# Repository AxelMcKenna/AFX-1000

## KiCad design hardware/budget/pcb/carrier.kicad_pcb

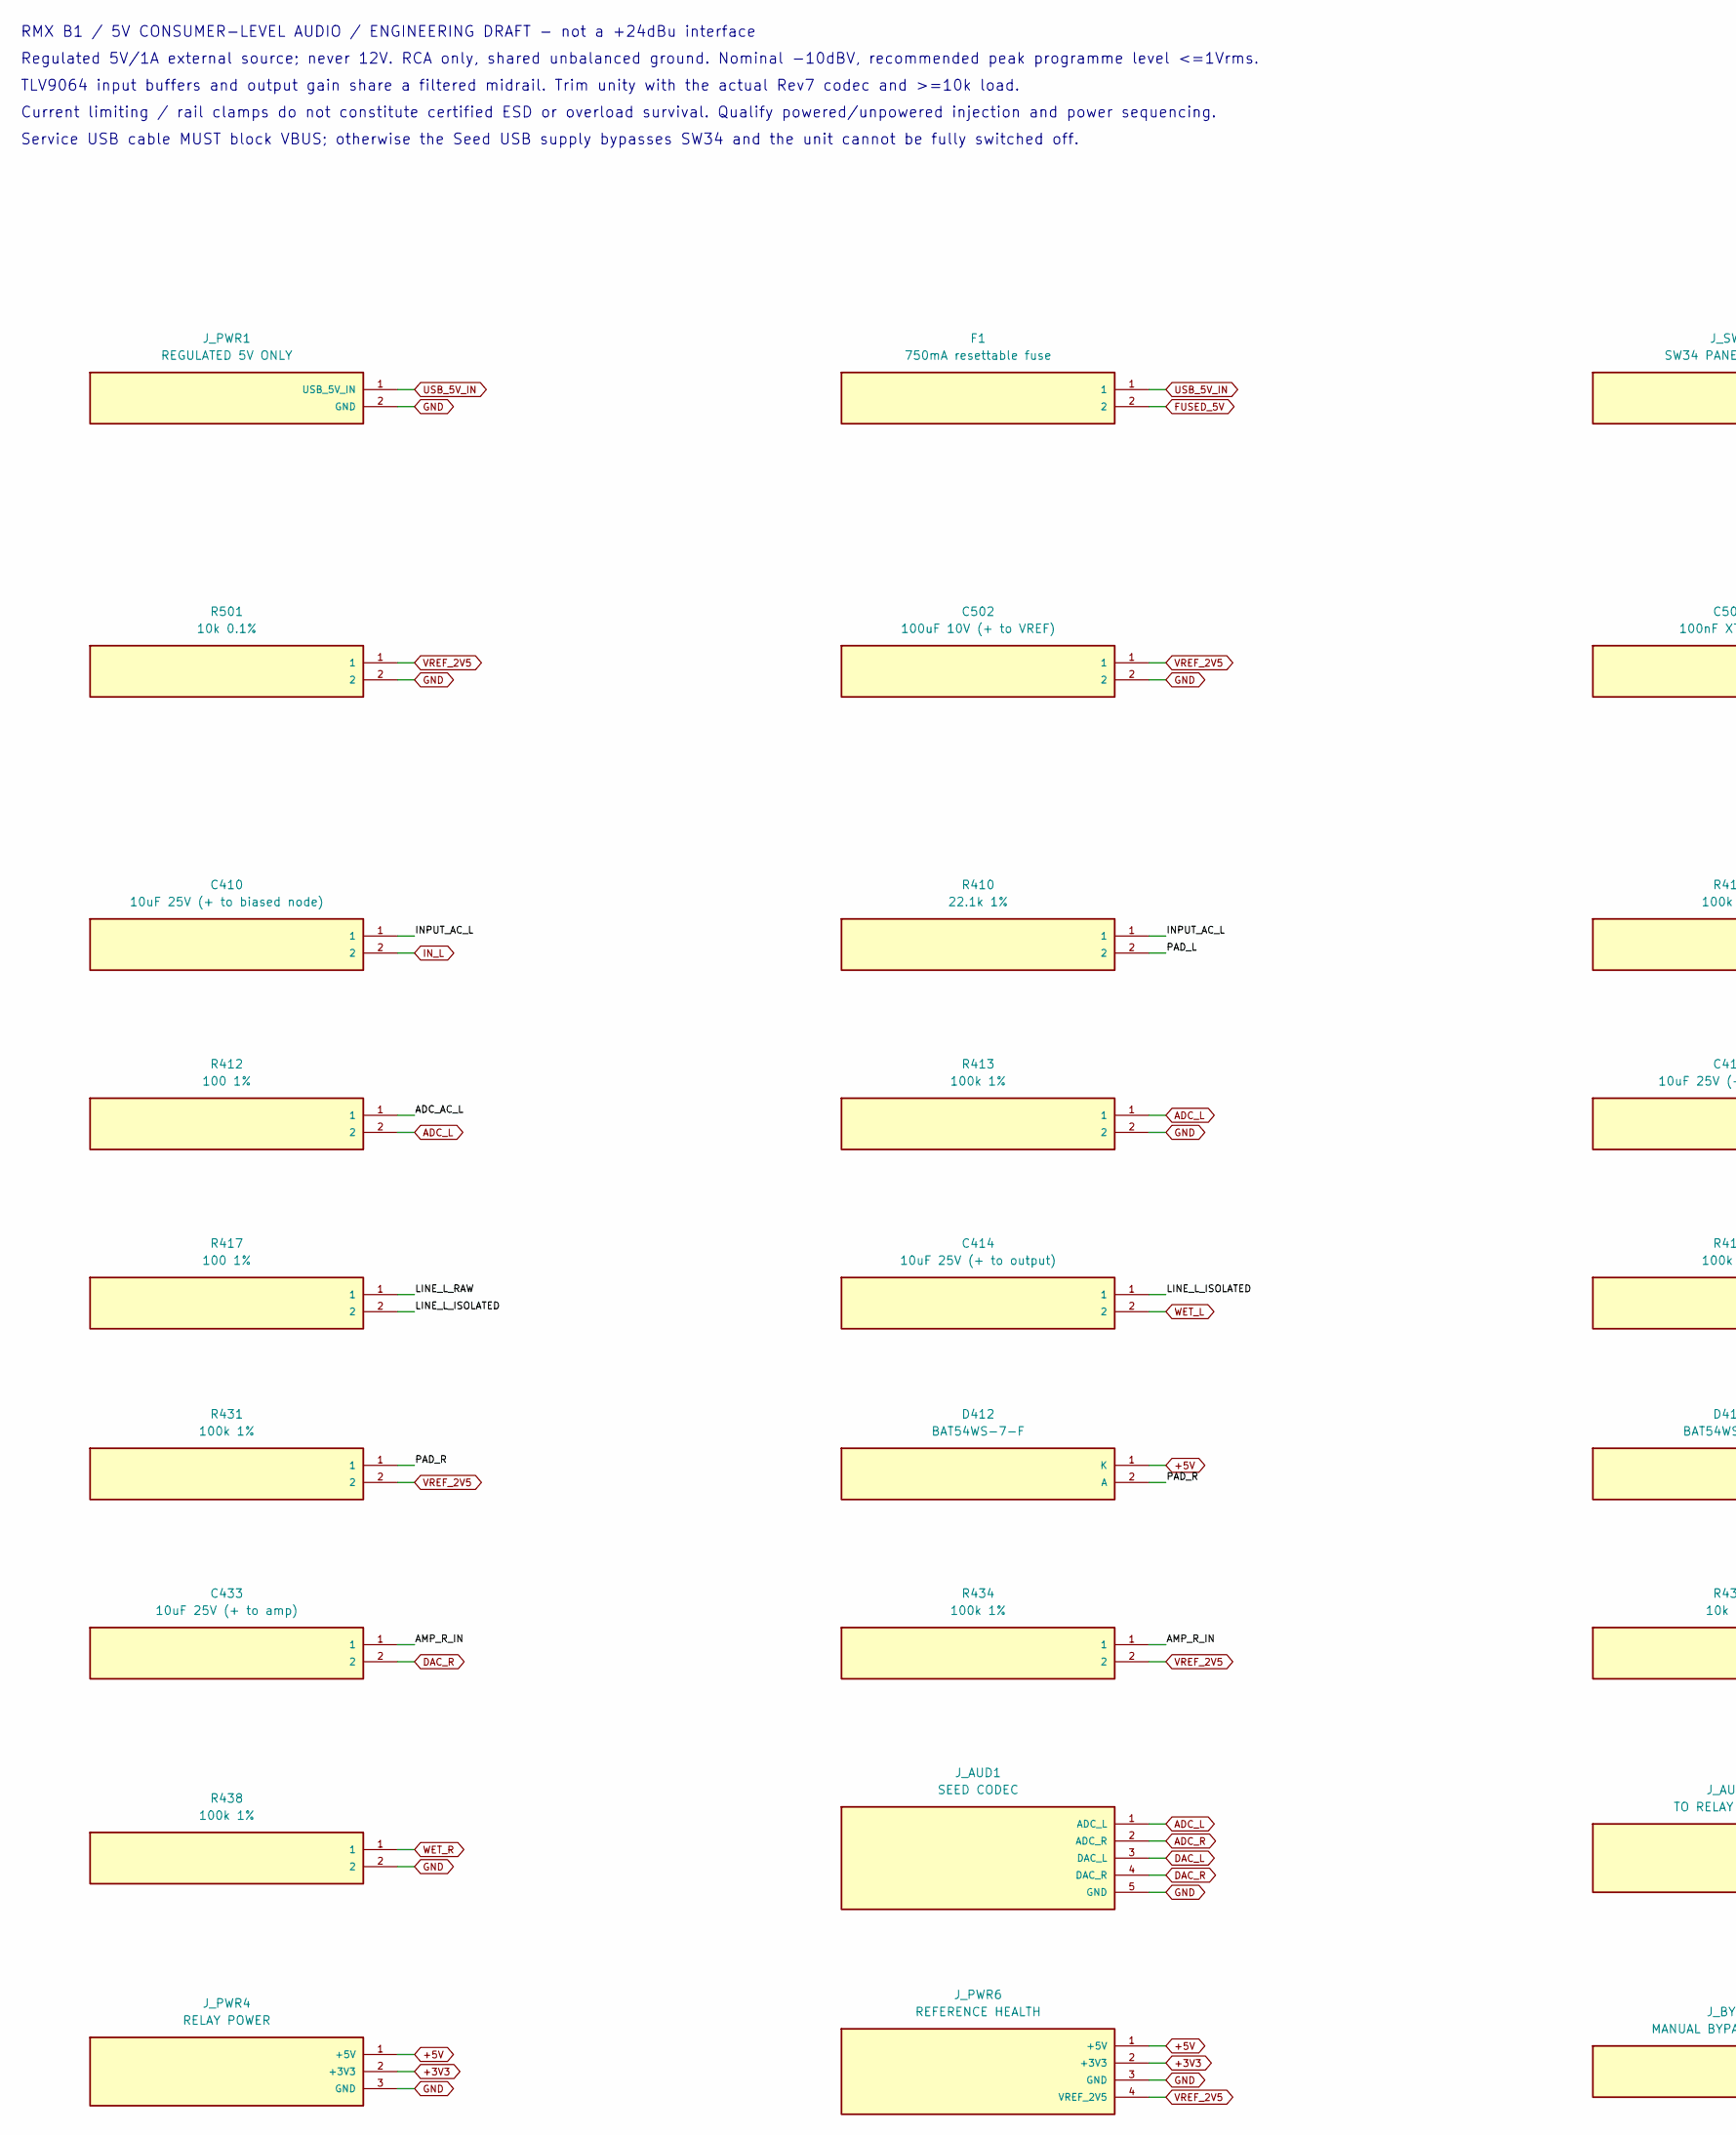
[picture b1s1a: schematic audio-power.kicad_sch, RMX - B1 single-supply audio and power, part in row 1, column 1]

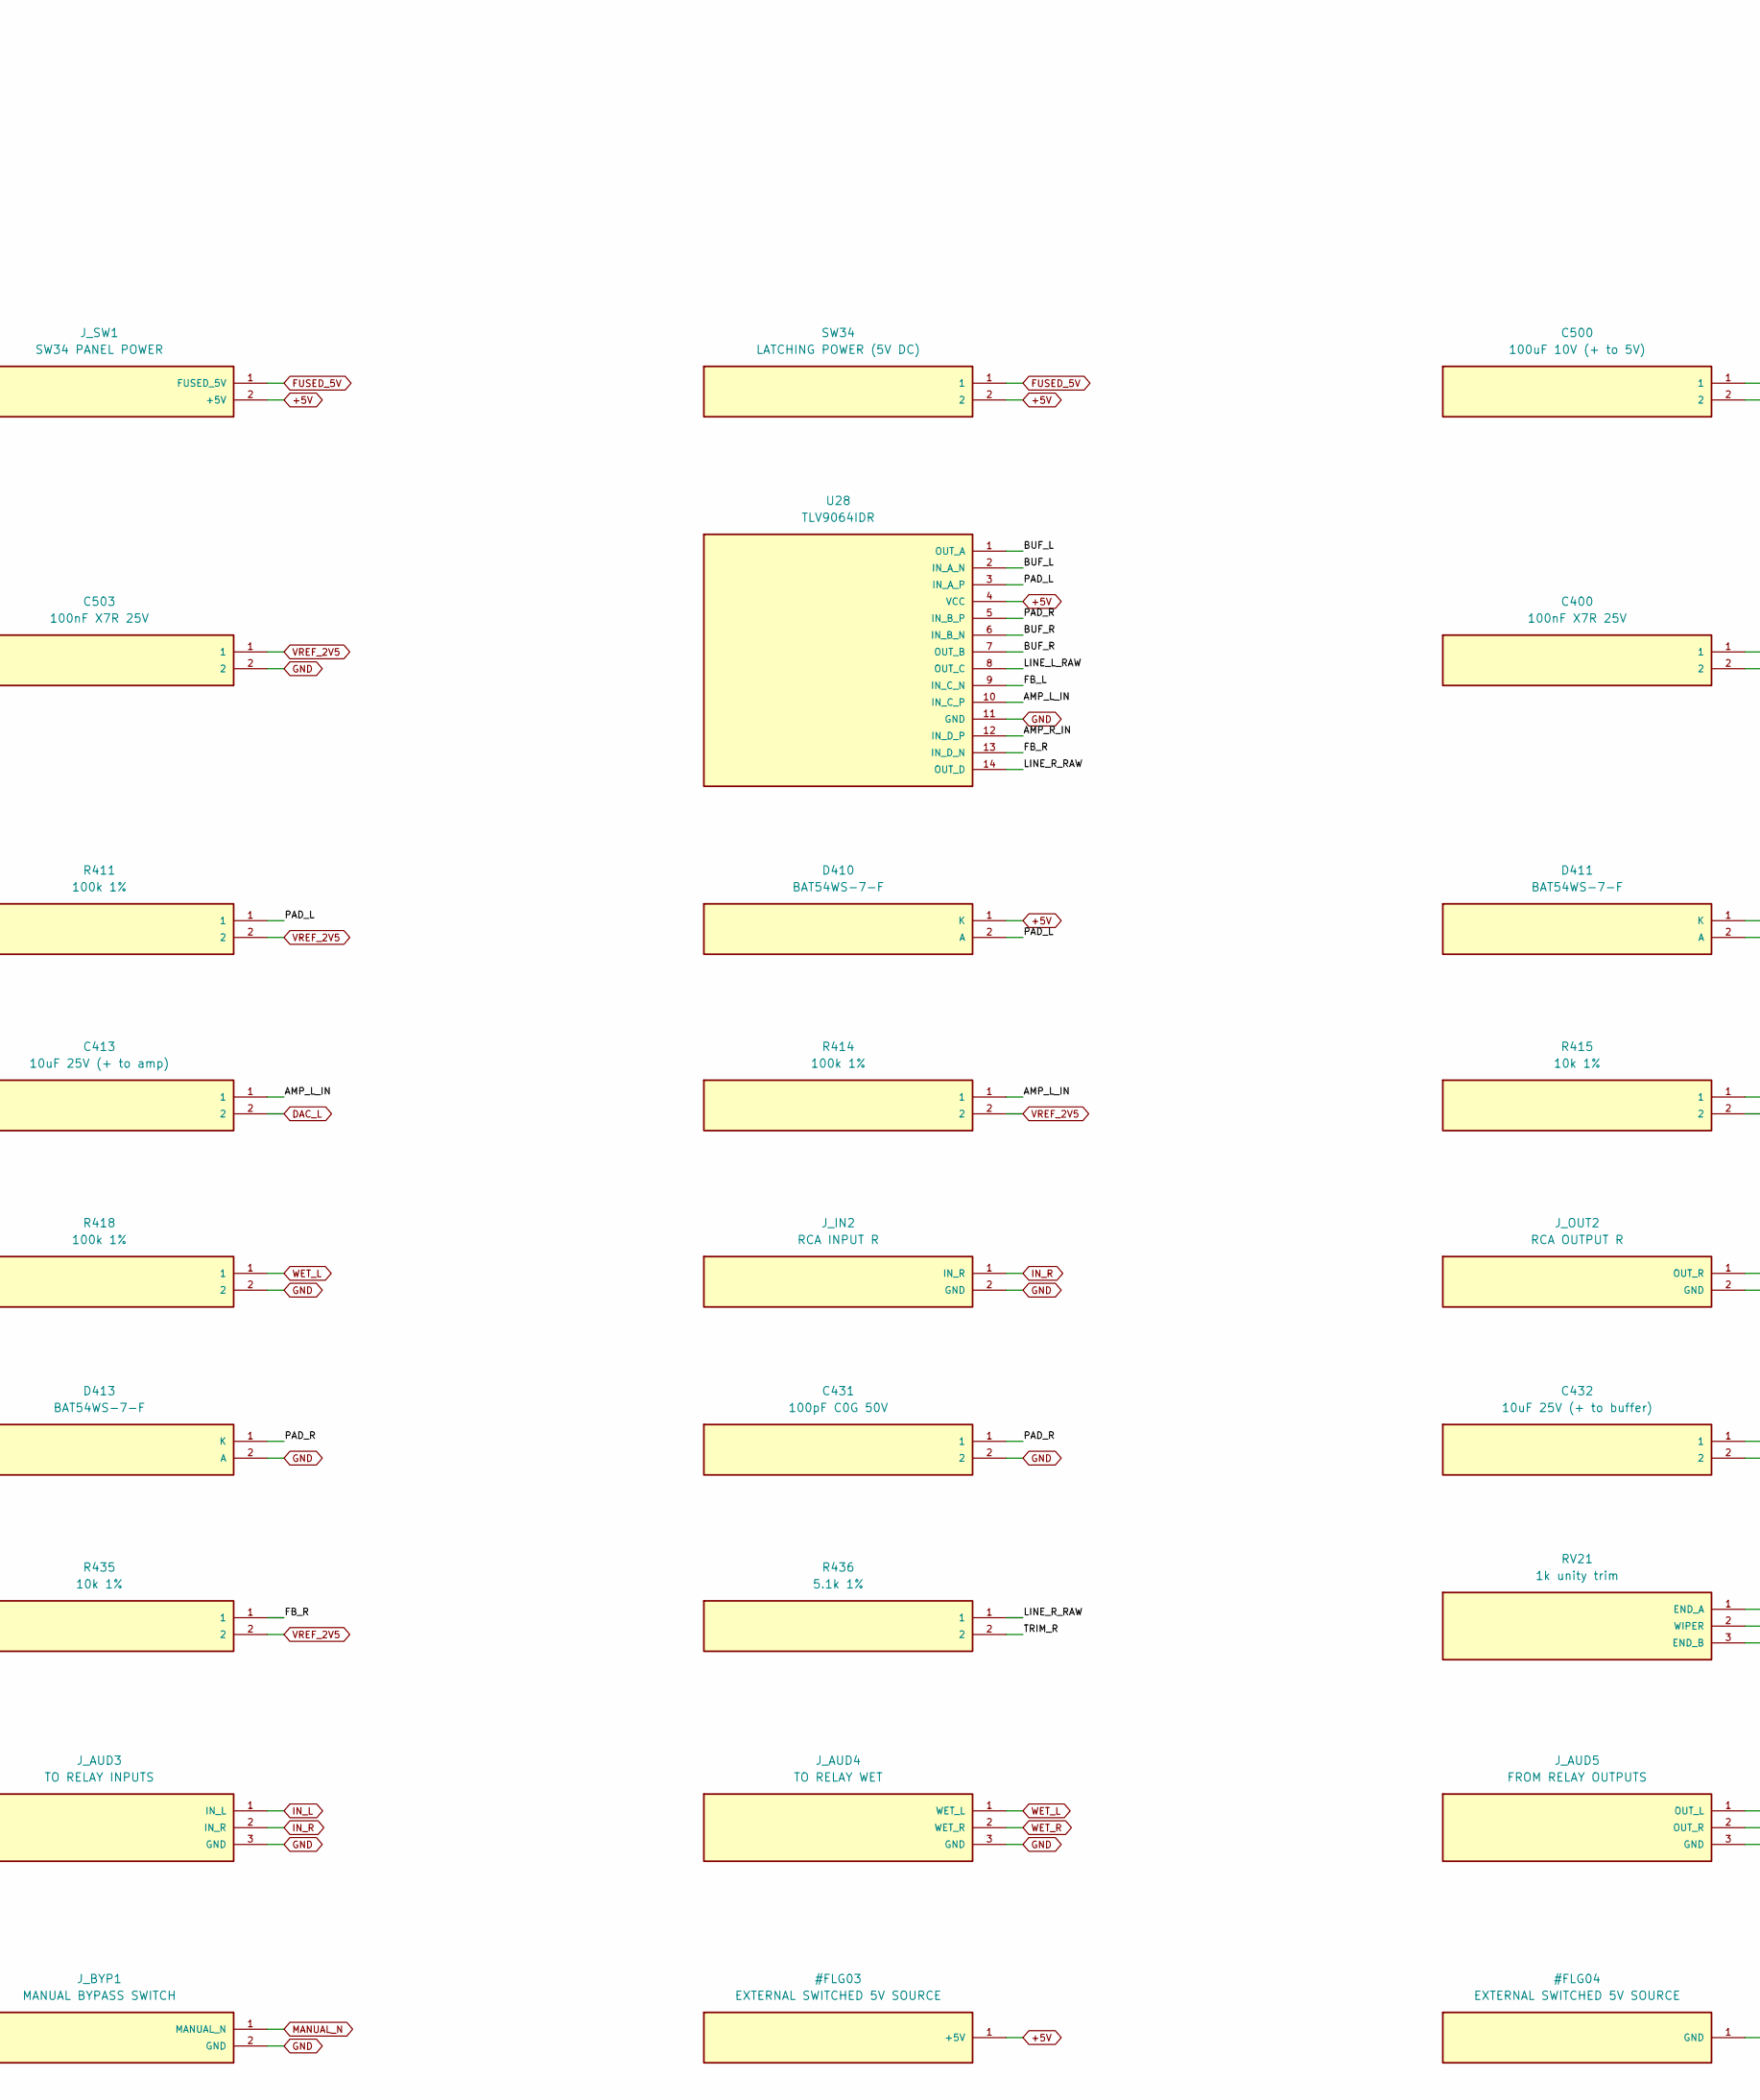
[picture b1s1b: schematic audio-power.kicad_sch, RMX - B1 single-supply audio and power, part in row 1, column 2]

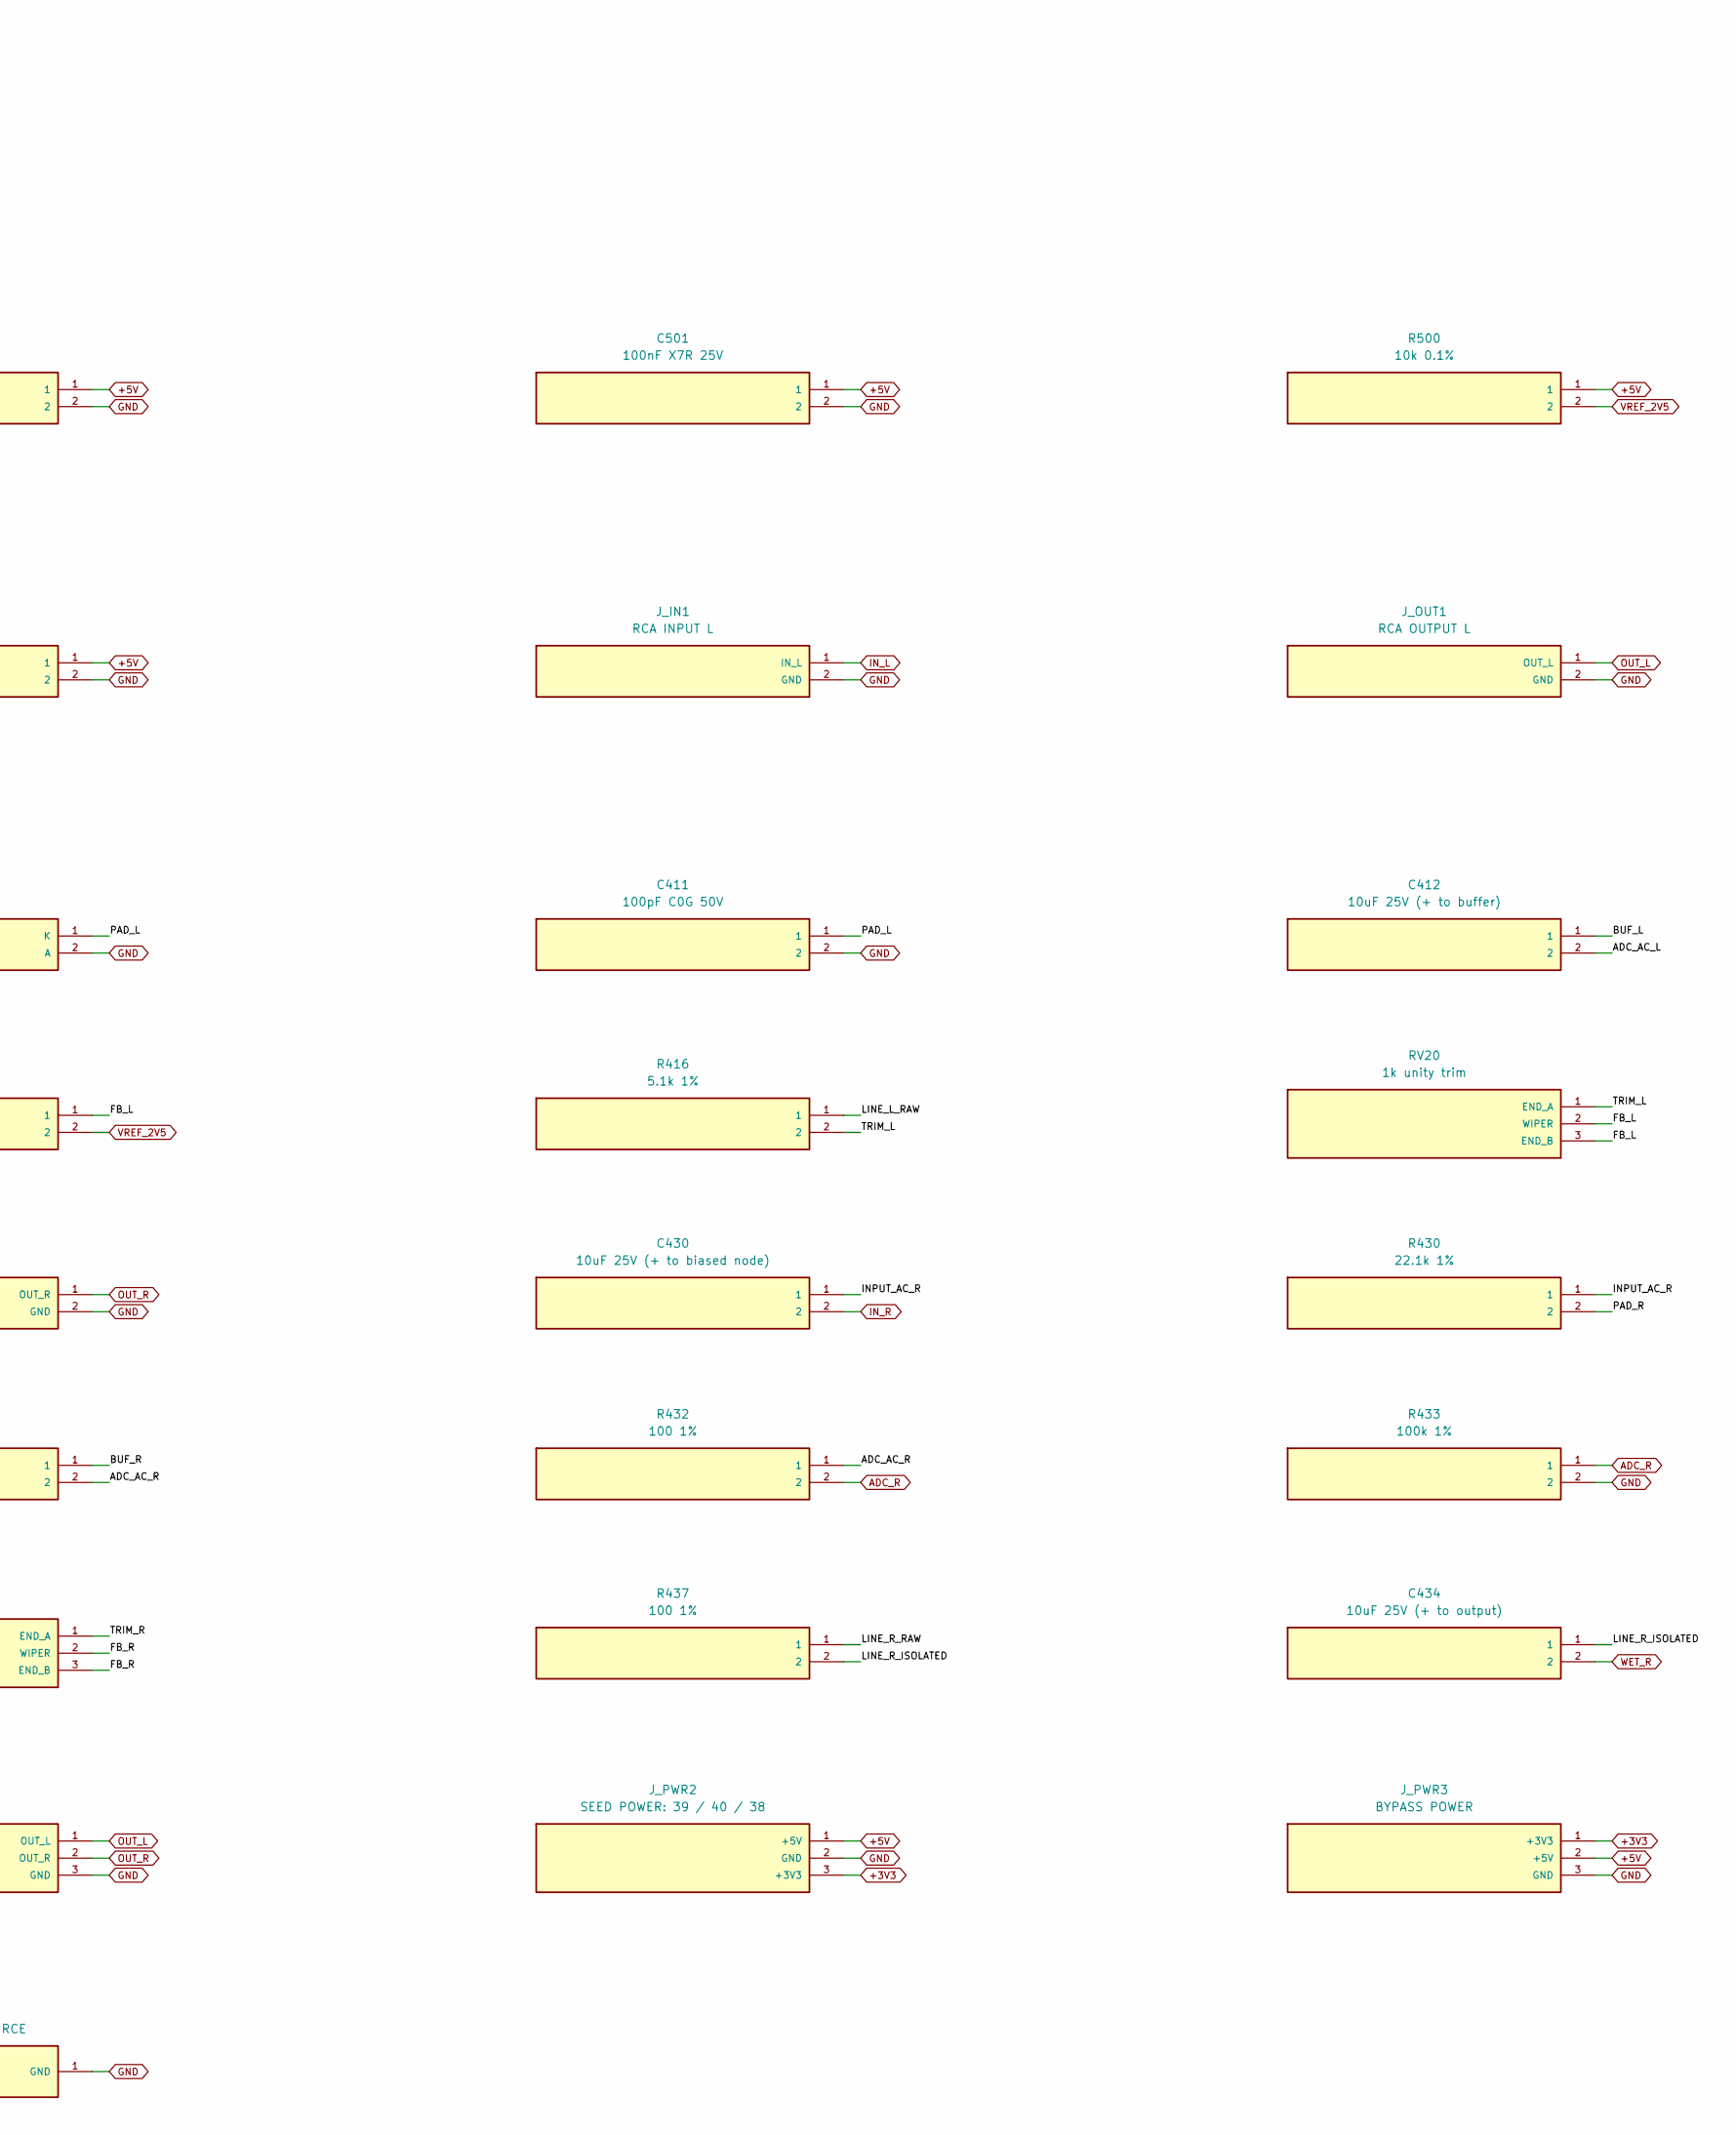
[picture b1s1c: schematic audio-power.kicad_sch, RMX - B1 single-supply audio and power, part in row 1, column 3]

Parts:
C400, C501, C503: 100nF X7R 25V; C_0805_2012Metric
C410, C430: 10uF 25V (+ to biased node); CP_Radial_D5.0mm_P2.00mm; MPN ECA-1EM100
C411, C431: 100pF C0G 50V; C_0805_2012Metric
C412, C432: 10uF 25V (+ to buffer); CP_Radial_D5.0mm_P2.00mm; MPN ECA-1EM100
C413, C433: 10uF 25V (+ to amp); CP_Radial_D5.0mm_P2.00mm; MPN ECA-1EM100
C414, C434: 10uF 25V (+ to output); CP_Radial_D5.0mm_P2.00mm; MPN ECA-1EM100
C500: 100uF 10V (+ to 5V); CP_Radial_D6.3mm_P2.50mm; MPN EEU-FR1A101
C502: 100uF 10V (+ to VREF); CP_Radial_D6.3mm_P2.50mm; MPN EEU-FR1A101
D410, D411, D412, D413: BAT54WS-7-F; D_SOD-323; MPN BAT54WS-7-F
F1: 750mA resettable fuse; Fuse_1206_3216Metric; MPN 1206L075YR
J_AUD1: SEED CODEC; PinHeader_1x05_P2.54mm_Vertical
J_AUD3: TO RELAY INPUTS; PinHeader_1x03_P2.54mm_Vertical
J_AUD4: TO RELAY WET; PinHeader_1x03_P2.54mm_Vertical
J_AUD5: FROM RELAY OUTPUTS; PinHeader_1x03_P2.54mm_Vertical
J_BYP1: MANUAL BYPASS SWITCH; PinHeader_1x02_P2.54mm_Vertical
J_IN1: RCA INPUT L; PinHeader_1x02_P2.54mm_Vertical
J_IN2: RCA INPUT R; PinHeader_1x02_P2.54mm_Vertical
J_OUT1: RCA OUTPUT L; PinHeader_1x02_P2.54mm_Vertical
J_OUT2: RCA OUTPUT R; PinHeader_1x02_P2.54mm_Vertical
J_PWR1: REGULATED 5V ONLY; PinHeader_1x02_P2.54mm_Vertical
J_PWR2: SEED POWER: 39 / 40 / 38; PinHeader_1x03_P2.54mm_Vertical
J_PWR3: BYPASS POWER; PinHeader_1x03_P2.54mm_Vertical
J_PWR4: RELAY POWER; PinHeader_1x03_P2.54mm_Vertical
J_PWR6: REFERENCE HEALTH; PinHeader_1x04_P2.54mm_Vertical
J_SW1: SW34 PANEL POWER; PinHeader_1x02_P2.54mm_Vertical
R410, R430: 22.1k 1%; R_0603_1608Metric; MPN RC0603FR-0722K1L
R411, R413, R414, R418, R431, R433, R434, R438: 100k 1%; R_0603_1608Metric; MPN RC0603FR-07100KL
R412, R417, R432, R437: 100 1%; R_0603_1608Metric; MPN RC0603FR-07100RL
R415, R435: 10k 1%; R_0603_1608Metric; MPN RC0603FR-0710KL
R416, R436: 5.1k 1%; R_0603_1608Metric; MPN RC0603FR-075K1L
R500, R501: 10k 0.1%; R_0603_1608Metric; MPN RT0603BRD0710KL
RV20, RV21: 1k unity trim; Potentiometer_Bourns_3296W_Vertical; MPN 3296W-1-102LF
SW34: LATCHING POWER (5V DC)
U28: TLV9064IDR; SOIC-14_3.9x8.7mm_P1.27mm; MPN TLV9064IDR

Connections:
+3V3: J_PWR2.3 (+3V3), J_PWR3.1 (+3V3), J_PWR4.2 (+3V3), J_PWR6.2 (+3V3); also elsewhere on the board
+5V: C400.1, C500.1, C501.1, D410.1 (K), D412.1 (K), J_PWR2.1 (+5V), J_PWR3.2 (+5V), J_PWR4.1 (+5V), J_PWR6.1 (+5V), J_SW1.2 (+5V), R500.1, SW34.2, U28.4 (VCC); also elsewhere on the board
/audio-power/ADC_AC_L: C412.2, R412.1
/audio-power/ADC_AC_R: C432.2, R432.1
/audio-power/AMP_L_IN: C413.1, R414.1, U28.10 (IN_C_P)
/audio-power/AMP_R_IN: C433.1, R434.1, U28.12 (IN_D_P)
/audio-power/BUF_L: C412.1, U28.1 (OUT_A), U28.2 (IN_A_N)
/audio-power/BUF_R: C432.1, U28.6 (IN_B_N), U28.7 (OUT_B)
/audio-power/FB_L: R415.1, RV20.2 (WIPER), RV20.3 (END_B), U28.9 (IN_C_N)
/audio-power/FB_R: R435.1, RV21.2 (WIPER), RV21.3 (END_B), U28.13 (IN_D_N)
/audio-power/INPUT_AC_L: C410.1, R410.1
/audio-power/INPUT_AC_R: C430.1, R430.1
/audio-power/LINE_L_ISOLATED: C414.1, R417.2
/audio-power/LINE_L_RAW: R416.1, R417.1, U28.8 (OUT_C)
/audio-power/LINE_R_ISOLATED: C434.1, R437.2
/audio-power/LINE_R_RAW: R436.1, R437.1, U28.14 (OUT_D)
/audio-power/PAD_L: C411.1, D410.2 (A), D411.1 (K), R410.2, R411.1, U28.3 (IN_A_P)
/audio-power/PAD_R: C431.1, D412.2 (A), D413.1 (K), R430.2, R431.1, U28.5 (IN_B_P)
/audio-power/TRIM_L: R416.2, RV20.1 (END_A)
/audio-power/TRIM_R: R436.2, RV21.1 (END_A)
ADC_L: J_AUD1.1 (ADC_L), R412.2, R413.1
ADC_R: J_AUD1.2 (ADC_R), R432.2, R433.1
DAC_L: C413.2, J_AUD1.3 (DAC_L)
DAC_R: C433.2, J_AUD1.4 (DAC_R)
FUSED_5V: F1.2, J_SW1.1 (FUSED_5V), SW34.1
GND: C400.2, C411.2, C431.2, C500.2, C501.2, C502.2, C503.2, D411.2 (A), D413.2 (A), J_AUD1.5 (GND), J_AUD3.3 (GND), J_AUD4.3 (GND), J_AUD5.3 (GND), J_BYP1.2 (GND), J_IN1.2 (GND), J_IN2.2 (GND), J_OUT1.2 (GND), J_OUT2.2 (GND), J_PWR1.2 (GND), J_PWR2.2 (GND), J_PWR3.3 (GND), J_PWR4.3 (GND), J_PWR6.3 (GND), R413.2, R418.2, R433.2, R438.2, R501.2, U28.11 (GND); also elsewhere on the board
IN_L: C410.2, J_AUD3.1 (IN_L), J_IN1.1 (IN_L); also elsewhere on the board
IN_R: C430.2, J_AUD3.2 (IN_R), J_IN2.1 (IN_R); also elsewhere on the board
MANUAL_N: J_BYP1.1 (MANUAL_N); also elsewhere on the board
OUT_L: J_AUD5.1 (OUT_L), J_OUT1.1 (OUT_L); also elsewhere on the board
OUT_R: J_AUD5.2 (OUT_R), J_OUT2.1 (OUT_R); also elsewhere on the board
USB_5V_IN: F1.1, J_PWR1.1 (USB_5V_IN)
VREF_2V5: C502.1, C503.1, J_PWR6.4 (VREF_2V5), R411.2, R414.2, R415.2, R431.2, R434.2, R435.2, R500.2, R501.1; also elsewhere on the board
WET_L: C414.2, J_AUD4.1 (WET_L), R418.1; also elsewhere on the board
WET_R: C434.2, J_AUD4.2 (WET_R), R438.1; also elsewhere on the board

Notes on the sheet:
RMX B1 / 5V CONSUMER-LEVEL AUDIO / ENGINEERING DRAFT - not a +24dBu interface
Regulated 5V/1A external source; never 12V. RCA only, shared unbalanced ground. Nominal -10dBV, recommended peak programme level <=1Vrms.
TLV9064 input buffers and output gain share a filtered midrail. Trim unity with the actual Rev7 codec and >=10k load.
Current limiting / rail clamps do not constitute certified ESD or overload survival. Qualify powered/unpowered injection and power sequencing.
Service USB cable MUST block VBUS; otherwise the Seed USB supply bypasses SW34 and the unit cannot be fully switched off.
